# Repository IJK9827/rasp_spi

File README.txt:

Working code is in RaspberryPi-FreeRTOS-final.

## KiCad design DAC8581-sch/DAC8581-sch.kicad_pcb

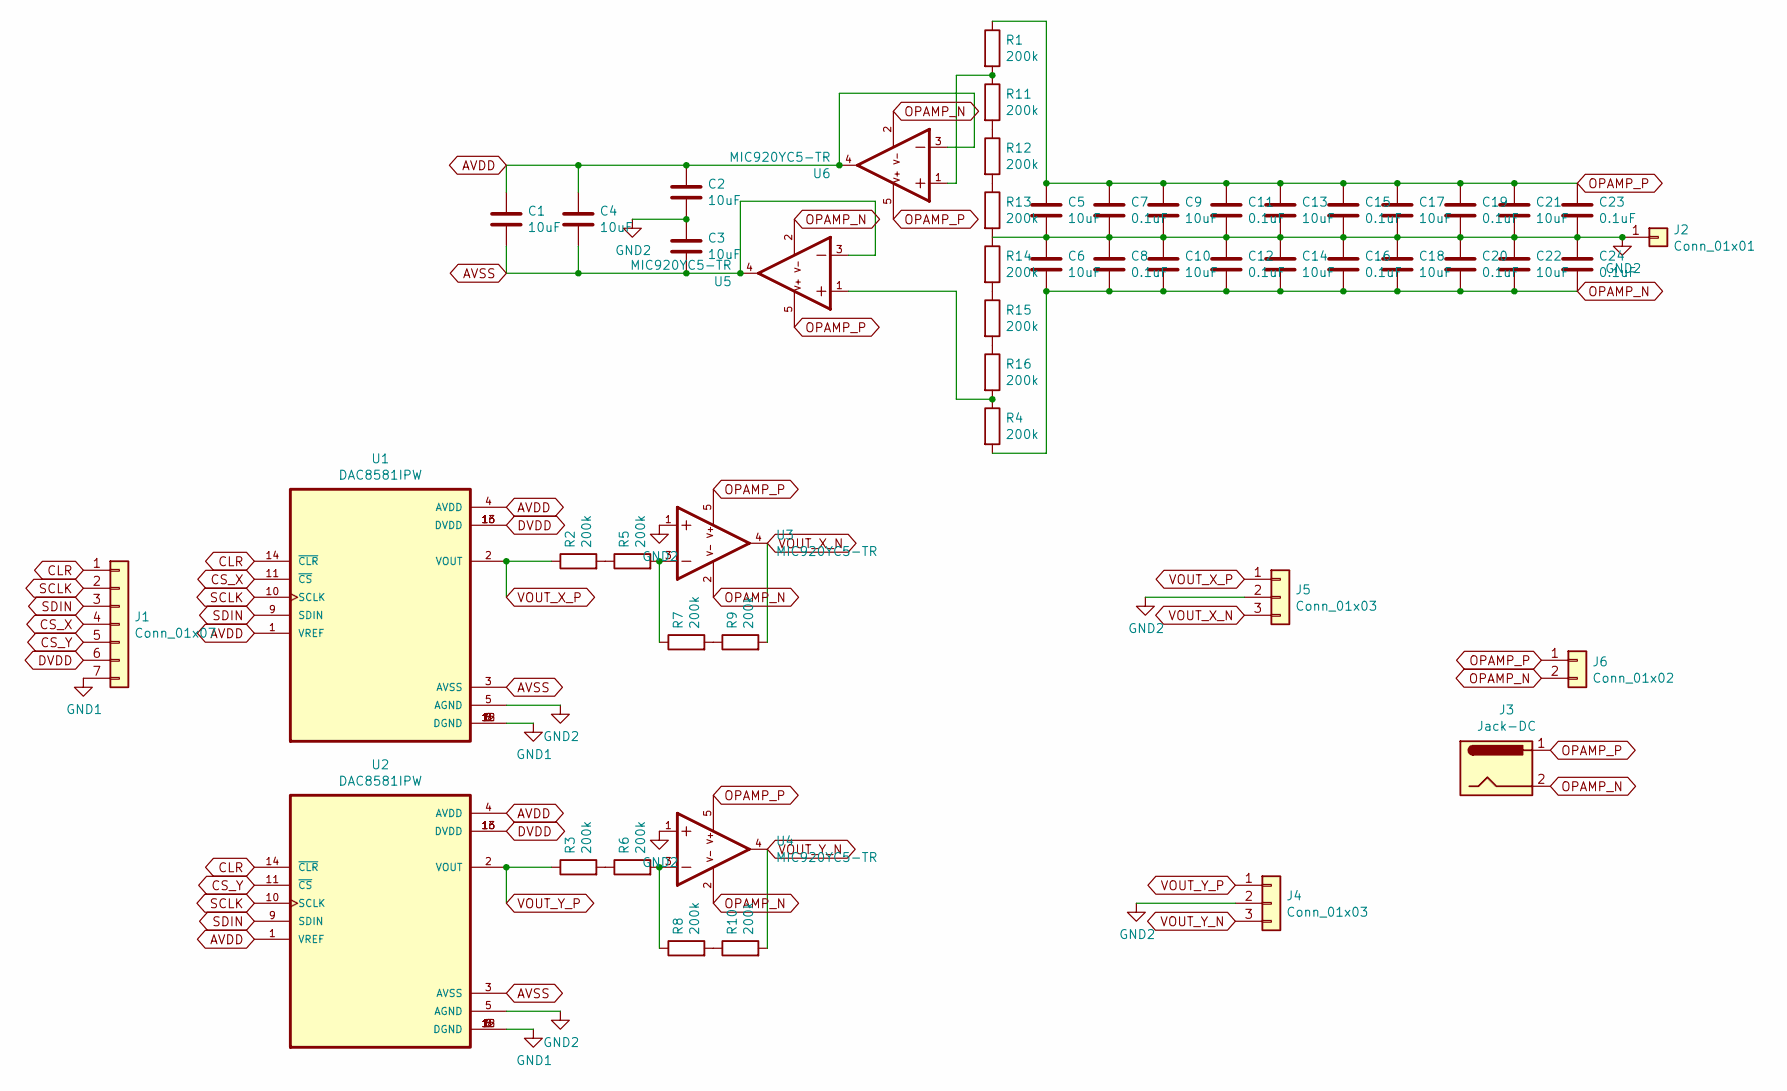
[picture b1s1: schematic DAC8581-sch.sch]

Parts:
C1, C2, C3, C4, C5, C6, C9, C10, C13, C14, C17, C18, C21, C22: 10uF; C_0603_1608Metric_Pad1.08x0.95mm_HandSolder
C7, C8, C11, C12, C15, C16, C19, C20, C23, C24: 0.1uF; C_0201_0603Metric_Pad0.64x0.40mm_HandSolder
J1: Conn_01x07; PinSocket_1x07_P2.54mm_Vertical
J2: Conn_01x01; PinSocket_1x01_P2.54mm_Vertical
J3: Jack-DC; BarrelJack_Horizontal
J4, J5: Conn_01x03; PinHeader_1x03_P2.54mm_Vertical
J6: Conn_01x02; PinSocket_1x02_P2.54mm_Vertical
R1, R2, R3, R4, R5, R6, R7, R8, R9, R10, R11, R12, R13, R14, R15, R16: 200k; R_0402_1005Metric_Pad0.72x0.64mm_HandSolder
U1, U2: DAC8581IPW; SOP65P640X120-16N
U3, U4, U5, U6: MIC920YC5-TR; SOT65P210X110-5N; PARTREV March 2006

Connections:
AVDD: C1.1, C2.1, C4.1, U1.1 (VREF), U1.4 (AVDD), U2.1 (VREF), U2.4 (AVDD), U6.3, U6.4
AVSS: C1.2, C3.2, C4.2, U1.3 (AVSS), U2.3 (AVSS), U5.3, U5.4
CLR: J1.1, U1.14 (~CLR), U2.14 (~CLR)
CS_X: J1.4, U1.11 (~CS)
CS_Y: J1.5, U2.11 (~CS)
DVDD: J1.6, U1.13 (DVDD), U1.16 (DVDD), U2.13 (DVDD), U2.16 (DVDD)
GND1: J1.7, U1.6 (DGND), U1.7 (DGND), U1.8 (DGND), U1.12 (DGND), U1.15 (DGND), U2.6 (DGND), U2.7 (DGND), U2.8 (DGND), U2.12 (DGND), U2.15 (DGND)
GND2: C2.2, C3.1, C5.2, C6.1, C7.2, C8.1, C9.2, C10.1, C11.2, C12.1, C13.2, C14.1, C15.2, C16.1, C17.2, C18.1, C19.2, C20.1, C21.2, C22.1, C23.2, C24.1, J2.1, J4.2, J5.2, R13.2, R14.1, U1.5 (AGND), U2.5 (AGND), U3.1, U4.1
unnamed: R1.2, R11.1, U6.1
unnamed: R2.2, R5.1
unnamed: R3.2, R6.1
unnamed: R5.2, R7.1, U3.3
unnamed: R6.2, R8.1, U4.3
unnamed: R7.2, R9.1
unnamed: R8.2, R10.1
unnamed: R11.2, R12.1
unnamed: R12.2, R13.1
unnamed: R14.2, R15.1
unnamed: R15.2, R16.1
unnamed: R4.1, R16.2, U5.1
OPAMP_N: C6.2, C8.2, C10.2, C12.2, C14.2, C16.2, C18.2, C20.2, C22.2, C24.2, J3.2, J6.2, R4.2, U3.2, U4.2, U5.2, U6.2
OPAMP_P: C5.1, C7.1, C9.1, C11.1, C13.1, C15.1, C17.1, C19.1, C21.1, C23.1, J3.1, J6.1, R1.1, U3.5, U4.5, U5.5, U6.5
SCLK: J1.2, U1.10 (SCLK), U2.10 (SCLK)
SDIN: J1.3, U1.9 (SDIN), U2.9 (SDIN)
VOUT_X_N: J5.3, R9.2, U3.4
VOUT_X_P: J5.1, R2.1, U1.2 (VOUT)
VOUT_Y_N: J4.3, R10.2, U4.4
VOUT_Y_P: J4.1, R3.1, U2.2 (VOUT)

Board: 2 copper layers, 52 parts (0 on the bottom side), 28 nets, no tracks yet.

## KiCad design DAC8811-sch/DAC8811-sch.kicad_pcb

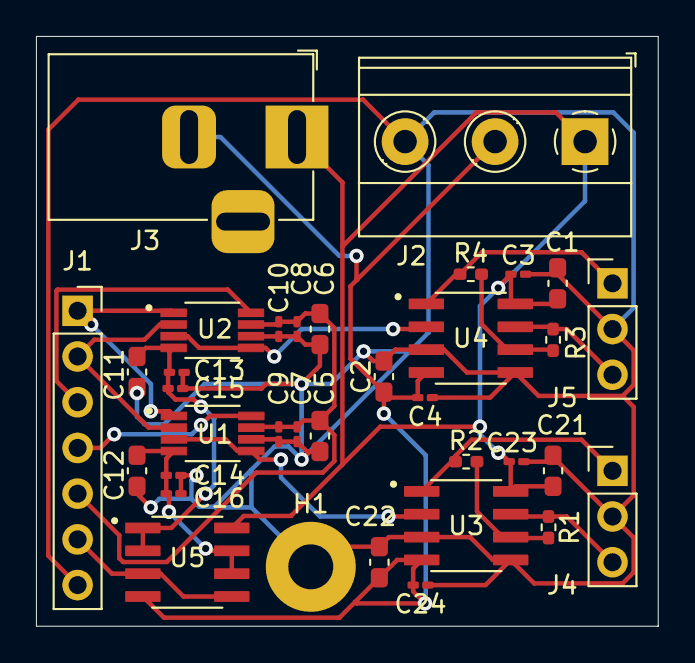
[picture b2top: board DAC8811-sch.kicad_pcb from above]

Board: 2 copper layers, 34.5 x 32.8 mm, 35 parts (0 on the bottom side), 19 nets.

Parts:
C1, C2, C5, C6, C11, C12, C21, C22: 10uF; C_0603_1608Metric_Pad1.08x0.95mm_HandSolder
C3, C4, C7, C8, C13, C14, C23, C24: 0.1uF; C_0201_0603Metric_Pad0.64x0.40mm_HandSolder
C9, C10, C15, C16: 1nF; C_0201_0603Metric_Pad0.64x0.40mm_HandSolder
H1: MountingHole_Pad; MountingHole_2.5mm_Pad
J1: Conn_01x07; PinSocket_1x07_P2.54mm_Vertical
J2: Screw_Terminal_01x03; TerminalBlock_Phoenix_MKDS-1,5-3_1x03_P5.00mm_Horizontal
J3: Jack-DC; BarrelJack_Horizontal
J4, J5: Conn_01x03; PinHeader_1x03_P2.54mm_Vertical
R1, R2, R3, R4: 10k; R_0402_1005Metric_Pad0.72x0.64mm_HandSolder
U1, U2: DAC8811IBDGKR; SOP65P490X110-8N
U3, U4, U5: OPA2277UA_2K5; SOIC127P599X175-8N

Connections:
5V: J1.6, U5.3, U5.5
CS_X: J1.3, U2.8
CS_Y: J1.4, U1.8
DVDD: C5.1, C6.1, C7.1, C8.1, C9.1, C10.1, J1.5, U1.7, U2.7
GND1: C1.2, C2.1, C3.2, C4.1, C5.2, C6.2, C7.2, C8.2, C9.2, C10.2, C11.2, C12.2, C13.2, C14.2, C15.2, C16.2, C21.2, C22.1, C23.2, C24.1, H1.1, J1.7, J2.3, J4.2, J5.2, U1.6, U2.6, U3.3, U3.5, U4.3, U4.5
unnamed: R1.2, R2.2, U3.6
unnamed: R3.2, R4.2, U4.6
unnamed: U1.3, U1.5, U3.2
unnamed: U2.3, U2.5, U4.2
OPAMP_N: C2.2, C4.2, C22.2, C24.2, J2.2, J3.2, U3.4, U4.4, U5.4
OPAMP_P: C1.1, C3.1, C21.1, C23.1, J2.1, J3.1, U3.8, U4.8, U5.8
SCLK: J1.1, U1.1, U2.1
SDIN: J1.2, U1.2, U2.2
VOUT_X_N: J5.3, R3.1, U4.7
VOUT_X_P: J5.1, R4.1, U4.1
VOUT_Y_N: J4.3, R1.1, U3.7
VOUT_Y_P: J4.1, R2.1, U3.1
Vref_x: C11.1, C13.1, C15.1, U2.4, U5.1, U5.2
Vref_y: C12.1, C14.1, C16.1, U1.4, U5.6, U5.7
